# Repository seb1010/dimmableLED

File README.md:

# Dimmable LEDs
Low voltage led lights designed to be strung in parallel. The brightness is controlled by amplitude modulation of a 500 Hz signal placed on top of the DC supply rail. 

## Features
* Output power adjustable from 100mW to 3-5 Watts (depending on how hot you want the junctions)
* Protection against reverse polarity connection
* Protection against supply under voltage
* With proper implementation, resistance of cable has a negligible effect on brightness
* Fast rising startup edges and brief voltage spikes have no major effect

## Theory of Operation
These lights take advantage of the fact that the ac imput impedance of each light is essentially infinite. The wires by comparason have very little impedance so there is negligiable voltage division even with impactical wire lengths.

### Signal Path
The rectified and then low pass filtered ac signal is used as the "voltage reference" for a constant current driver for the LEDs. The signal goes throught the following path.
1. ac coupling capacitor is used to remove the dc supply voltage
2. decoupled signal is amplified by a non-inverting amplifier with a gain of about 10
  * because the signal oscillates around ground and no negative supply rail is provided to the opamp this has the effect of rectifying the signal, but with gain and no diode drop.
3. The rectified signal is low pass filtered with an RC of ~ 80ms
4. This filtered signal used as the reference voltage in the opamp transistor current source with an emitter resistor of 3.3 ohms

### Under Voltage Protection
If there is insuffiecient voltage to turn on the LED's, but the ac signal is provided the opamp will drive as much current into the base of the npn as it can. If the opamp was simply connected to the supply rail, 30mA * 30V is about a watt and that would likely be unacceptable for a soic 8 opamp. Instead the positive supply pin is conneceted to a 5k resistor which goes to Vcc with a 10k resistor from the supply pin to ground. This limits to max possible current throught the opamp to just 6 mA and max power for the opamp happens around 3mA giving 50mW a very safe figure. The resistor could dissipate 200 mW worst case which is below rating. This has the additional benifit of allowing the use of lower voltage opamps, or add additional safety margin to rated maximum supply voltage.

### Start Up
 Due to the low pass filter the startup is quite gentle even if the supply rail has a fast edge.

 Shown below is output current

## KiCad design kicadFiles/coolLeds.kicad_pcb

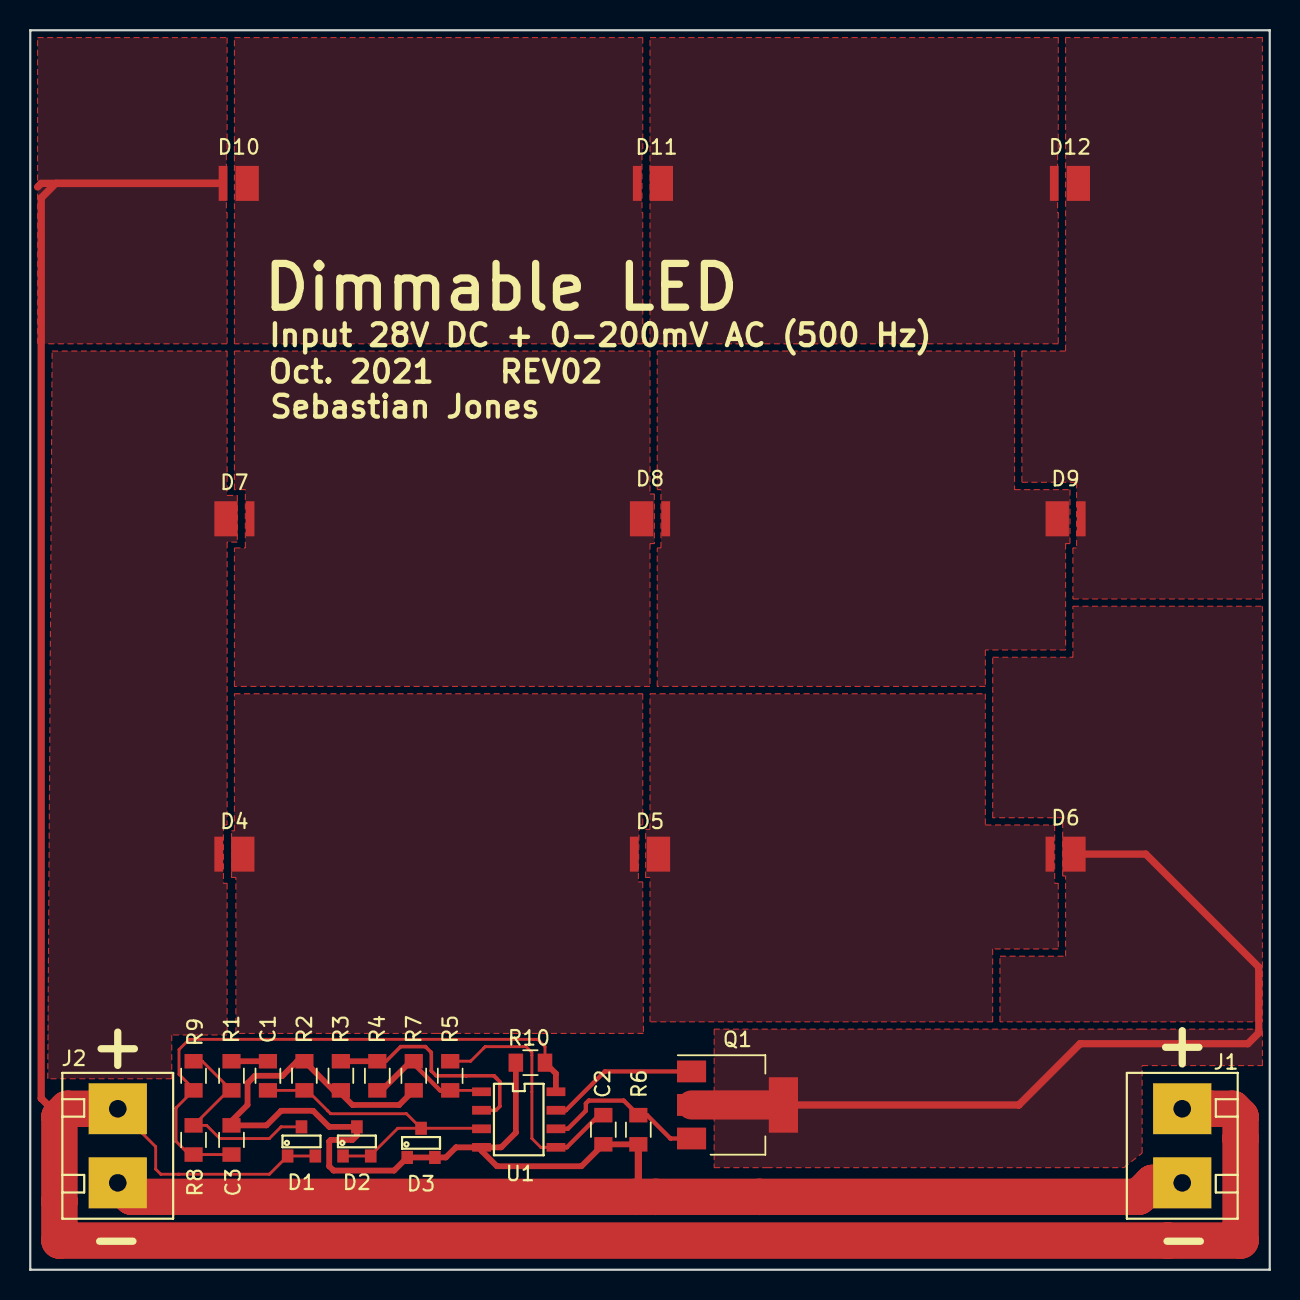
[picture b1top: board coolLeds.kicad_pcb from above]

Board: 2 copper layers, 85.0 x 85.0 mm, 29 parts (0 on the bottom side), 20 nets.

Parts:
C1, C2, C3: 1u; C_0805
D1, D2, D3: D; sot-23
D4, D5, D6, D7, D8, D9, D10, D11, D12: LED; cree_j_series_led
J1, J2: Conn_01x02; screwTerminal5.08_2
Q1: PZT2222A; SOT-223
R1: 100R; C_0805
R2, R3, R8, R9, R10: 10k; C_0805
R4, R5: 82k; C_0805
R6: 3R3; C_0805
R7: 560R; C_0805
U1: LM358; soic_8

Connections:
GND: C2.2, C3.2, D2.3, D3.1, D3.2, J1.2, J2.1, R2.1, R3.2, R6.1, R7.2, R10.2, U1.4
unnamed: C1.1, R1.1
unnamed: C1.2, D2.1, D2.2, D3.3, R2.2, U1.3
unnamed: C2.1, R5.1, U1.5
unnamed: C3.1, R8.2, R9.2, R10.1, U1.8
unnamed: D1.1, D1.2, D10.2, J1.1, J2.2
unnamed: D1.3, R1.2, R8.1, R9.1
unnamed: D4.1, D5.2
unnamed: D4.2, D7.1
unnamed: D5.1, D6.2
unnamed: D6.1, Q1.2, Q1.4
unnamed: D7.2, D8.1
unnamed: D8.2, D9.1
unnamed: D10.1, D11.2
unnamed: D11.1, D12.2
unnamed: D9.2, D12.1
unnamed: Q1.1, U1.7
unnamed: Q1.3, R6.2, U1.6
unnamed: R3.1, R4.2, U1.2
unnamed: R4.1, R5.2, R7.1, U1.1

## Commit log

2021-11-09 added cad files
2021-11-09 tried to add image
2021-11-09 renamed schematic
2021-11-09 formatting README
